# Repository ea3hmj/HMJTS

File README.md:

IMPORTANT, this repository is obsolete and has been replaced by the https://github.com/EA3HMJ-Tracking-Software-Suit

# EA3HMJ Antenna Tracking System

## Under construction
Please note that this is work-in-progress

## Description
This is an antenna tracking system that integrates dedicated hardware and software designed for amateur use in Earth–Moon–Earth communication (EME), radioastronomy, amateur Deep Sky Network (DSN) and other Space Communications applications where accurate and high precision tracking are required. 

Proper use of the system requires electronics knowledge and some software skills. Thus, it is only recommended to users with previous experience with antenna tracking systems.

The hardware components of this system are specifically selected to support the software applications that run on it. These components include a DishController unit -including a ESP32 microcontroller unit (MCU), DC motor driver board with high-performance and high-current driver devices, RS485 input/output devices and DC voltage step-up converter-, other peripherals like a variety of absolute digital encoders and inclinometers to sense the motion and position of the motorized slewing drive system and a remote-control unit.

In order to support single-turn and multiturn absolute encoders with parallel output interface there is also an optional Parallel to RS485 MODBUS converter board. Obviously, the latter is not needed if the sensors outputs are Modbus RS485 compliant.

The software components of this system are also specifically designed to work with the hardware components. This software includes the microcontroller and remote-control firmware, communications protocol, device drivers, and application software. 

The DishController MCU firmware controls and monitors the operation of the slewing drive motors, azimuth encoders, and elevation inclinometers.

The application software includes the DriverDish program, which is responsible for requesting data from the ephemeris server and communicating with the DishController unit, and a suite of server programs (JPLastroserver, Astroserver and Astronomyserver) that obtain the most accurate positioning data that is feasible and available from trustworthy sources. 

The integration of dedicated hardware and software in such a system provides several benefits. First, it improves system performance and reliability by allowing the DishController unit to directly access and control the specialized hardware components like the motor drivers and position sensors. This reduces overhead and improve response times. Second, it simplifies system design and development by providing a standardized set of hardware and software components that are optimized for narrow beamwidth antenna tracking. Third, in contrast to other antenna tracking system designs, the movement and position sensors are located at the last link of the movement chain to actively monitor the antenna's pointing direction. By doing so, the system is able to minimize the impact of mechanical tolerances and gear backslash.

The system is made up of three blocks that work together:
- Ephemeris servers ([Astroserver](https://github.com/ea3hmj/HMJTS/tree/main/ephemerides/astroserver), [JPLastroserver](https://github.com/ea3hmj/HMJTS/tree/main/ephemerides/JPLastroserver) and [Astronomyserver](https://github.com/ea3hmj/HMJTS/tree/main/ephemerides/astronmyserver))
- Control application in Windows OS ([DriverDish.App](https://github.com/ea3hmj/HMJTS/tree/main/DriverDish))
- Antenna Controller ([Controller Dish](https://github.com/ea3hmj/HMJTS/tree/main/controller%20dish/main%20board))

Utilities are also added:
- [AstroserverHelper.App](https://github.com/ea3hmj/HMJTS/tree/main/ephemerides/AstroserverHelper.App)
- Heatmap.App

## Disclaimer
This software -including the source and the whole package- and hardware are distributed "as is" without any representation or warranty of any kind, either express or implied. 

Please note that I am not able to provide support for this antenna tracking system. I designed and wrote it for myself and I am willing to share it here for those asking about my tracking system. I do not guarantee the accuracy or completeness of the information and materials distributed here. The software source has been tested on a real environment and scanned for viruses and has passed all tests.

I shall not be liable for any errors or omissions and shall not be responsible for any damages arising from the use of this antenna tracking system. I shall not be held responsible for any issues or problems that may arise from the use of it. 
By using any part of this antenna tracking system (software or hardware), you acknowledge and agree to the terms of this disclaimer.

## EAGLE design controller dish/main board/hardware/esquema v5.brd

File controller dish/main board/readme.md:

# CONTROLLER DISH
The controller allows to manage two motors with their corresponding position sensors.

## Documentation
For details, please read the document: [Dish Controller v4 ENG.pdf](docs/Dish%20Controller%20v4%20ENG.pdf)

## Disclaimer
This is a tracking systems designed for amateur use in Moonbounce, Radioastronomy and DSN. It requieres advanced skills of electronics and software, only recommended to users with previous experience with tracking systems.

Warning this software is distributed as is and I can not supply support. I write  it for myself and now I share it for other users that are asking about my tracking system.

This source and the whole package comes without warranty. It may or may not harm your computer or cell phone. Please use with care. Any damage cannot be related back to the author. The source has been tested on a real environment and scanned for viruses and has passed all tests.

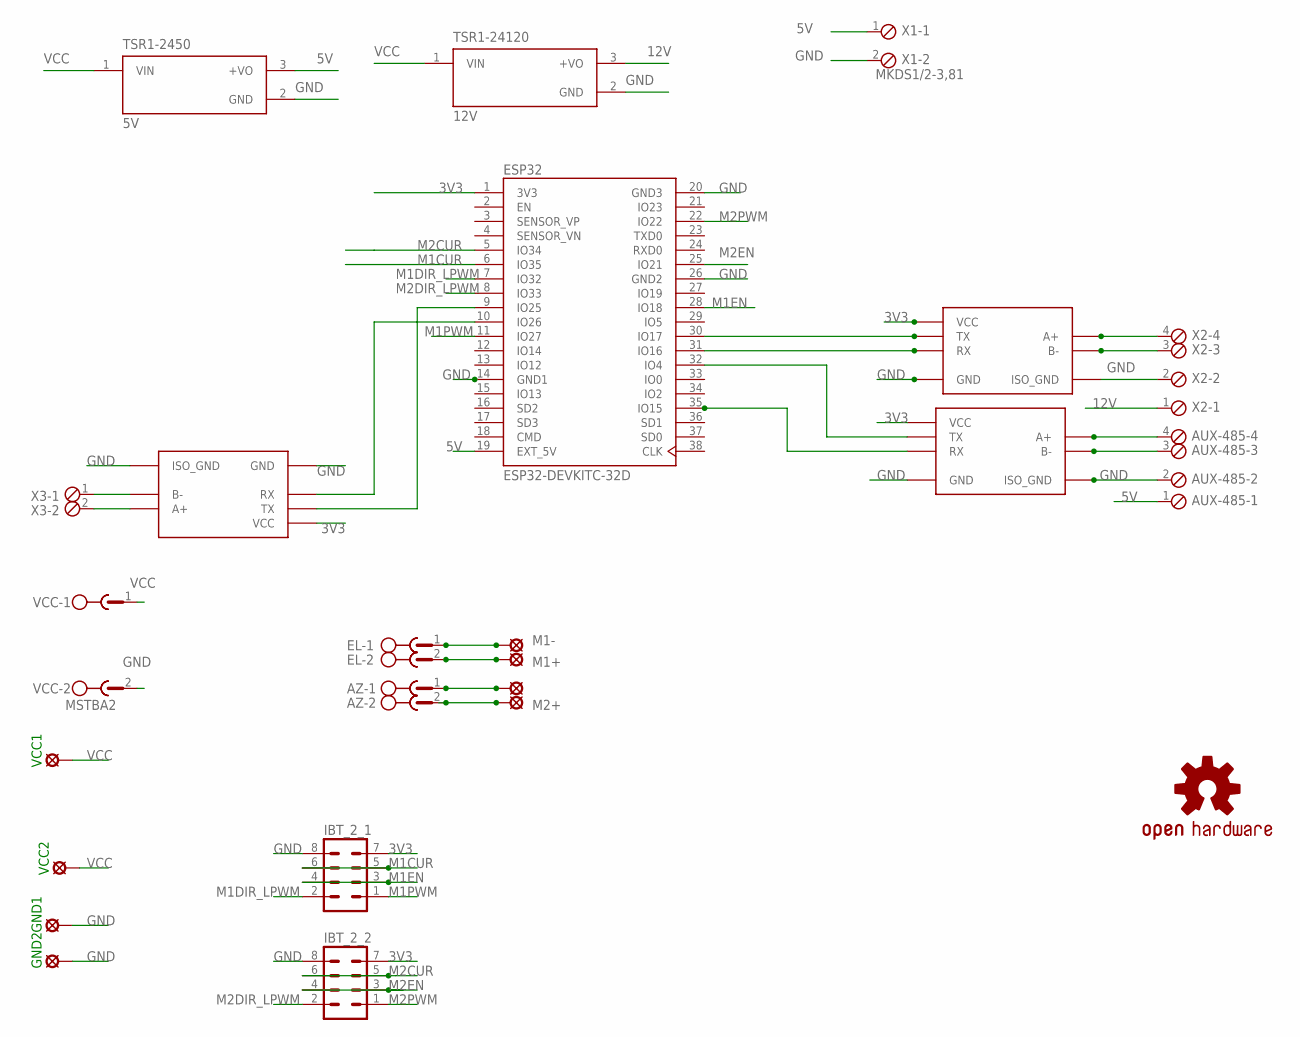
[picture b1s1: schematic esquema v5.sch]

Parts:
AUX-485: MKDS1/4-3,81; 4POL381
AZ: MSTBA2
EL: MSTBA2
ESP32: ESP32-DEVKITC-32D; MODULE_ESP32-DEVKITC-32D
GND1, GND2: LSP10
IBT_2_1: IBT_2_1; MA04-2
IBT_2_2: MA04-2
LOGO1: OSHW-LOGOMINI; OSHW-LOGO-MINI
M1+, M1-, M2+: LSP10
M2, M3, M4: LIMNOTECH_SMC_RS485
M2-: M2-; LSP10
TSR1-2450: 5V; CONV_K7803-500R3
TSR1-24120: 12V; CONV_K7803-500R3
VCC: MSTBA2
VCC1, VCC2: LSP10
X1, X3: MKDS1/2-3,81; 2POL381
X2: MKDS1/4-3,81; 4POL381

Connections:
3V3: ESP32.1 (3V3), IBT_2_1.7, IBT_2_2.7, M2.VCC, M3.VCC, M4.VCC
5V: AUX-485.1, ESP32.19 (EXT_5V), TSR1-2450.3 (+VO), X1.1
12V: TSR1-24120.3 (+VO), X2.1
GND: AUX-485.2, ESP32.14 (GND1), ESP32.20 (GND3), ESP32.26 (GND2), GND1.MP, GND2.MP, IBT_2_1.8, IBT_2_2.8, M2.GND, M2.GND_ISO (ISO_GND), M3.GND, M3.GND_ISO (ISO_GND), M4.GND, M4.GND_ISO (ISO_GND), TSR1-2450.2 (GND), TSR1-24120.2 (GND), VCC.2, X1.2, X2.2
M1+: EL.2, M1+.MP
M1-: EL.1, M1-.MP
M1CUR: ESP32.6 (IO35), IBT_2_1.5, IBT_2_1.6
M1DIR_LPWM: ESP32.7 (IO32), IBT_2_1.2
M1EN: ESP32.28 (IO18), IBT_2_1.3, IBT_2_1.4
M1PWM: ESP32.11 (IO27), IBT_2_1.1
M2+: AZ.2, M2+.MP
M2CUR: ESP32.5 (IO34), IBT_2_2.5, IBT_2_2.6
M2DIR_LPWM: ESP32.8 (IO33), IBT_2_2.2
M2EN: ESP32.25 (IO21), IBT_2_2.3, IBT_2_2.4
M2PWM: ESP32.22 (IO22), IBT_2_2.1
unnamed: M4.B-, X2.3
unnamed: AUX-485.4, M2.A+
unnamed: AZ.1, M2-.MP
unnamed: ESP32.32 (IO4), M2.TX
unnamed: ESP32.10 (IO26), M3.RX
unnamed: ESP32.9 (IO25), M3.TX
unnamed: ESP32.31 (IO16), M4.RX
unnamed: ESP32.30 (IO17), M4.TX
unnamed: M3.B-, X3.1
unnamed: M3.A+, X3.2
unnamed: ESP32.35 (IO15), M2.RX
unnamed: AUX-485.3, M2.B-
unnamed: M4.A+, X2.4
VCC: TSR1-2450.1 (VIN), TSR1-24120.1 (VIN), VCC.1, VCC1.MP, VCC2.MP

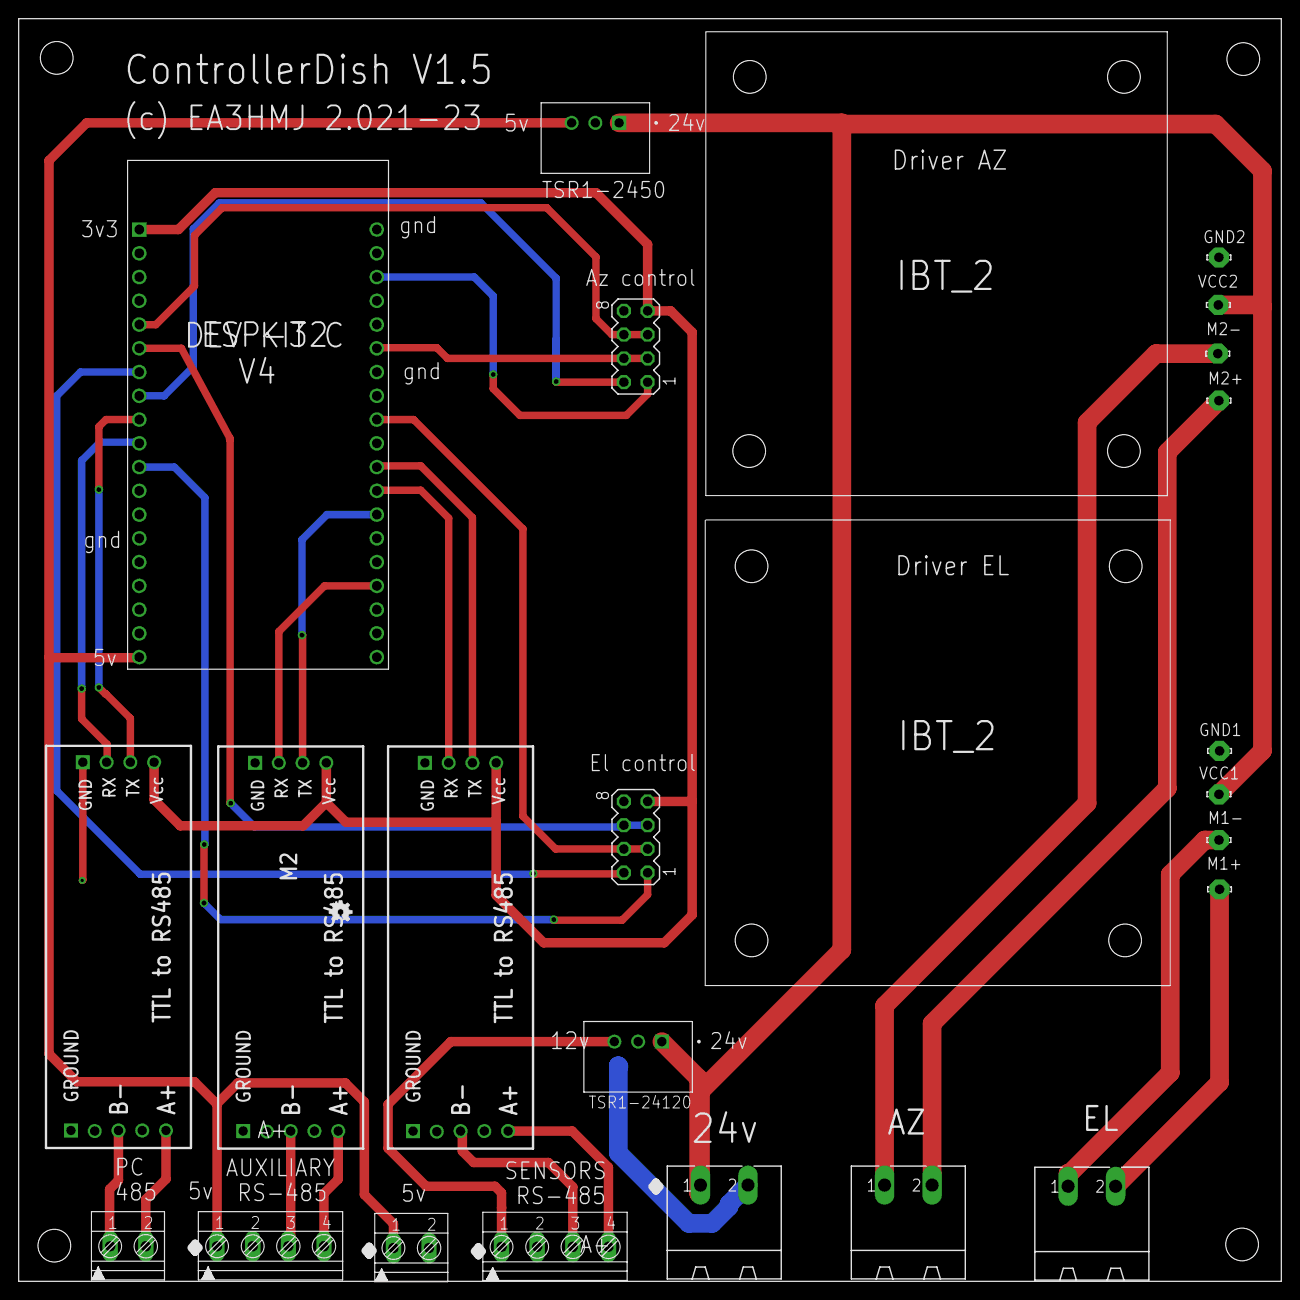
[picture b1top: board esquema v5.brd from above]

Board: 2 copper layers, 135.0 x 135.0 mm, 24 parts (0 on the bottom side), 29 nets.

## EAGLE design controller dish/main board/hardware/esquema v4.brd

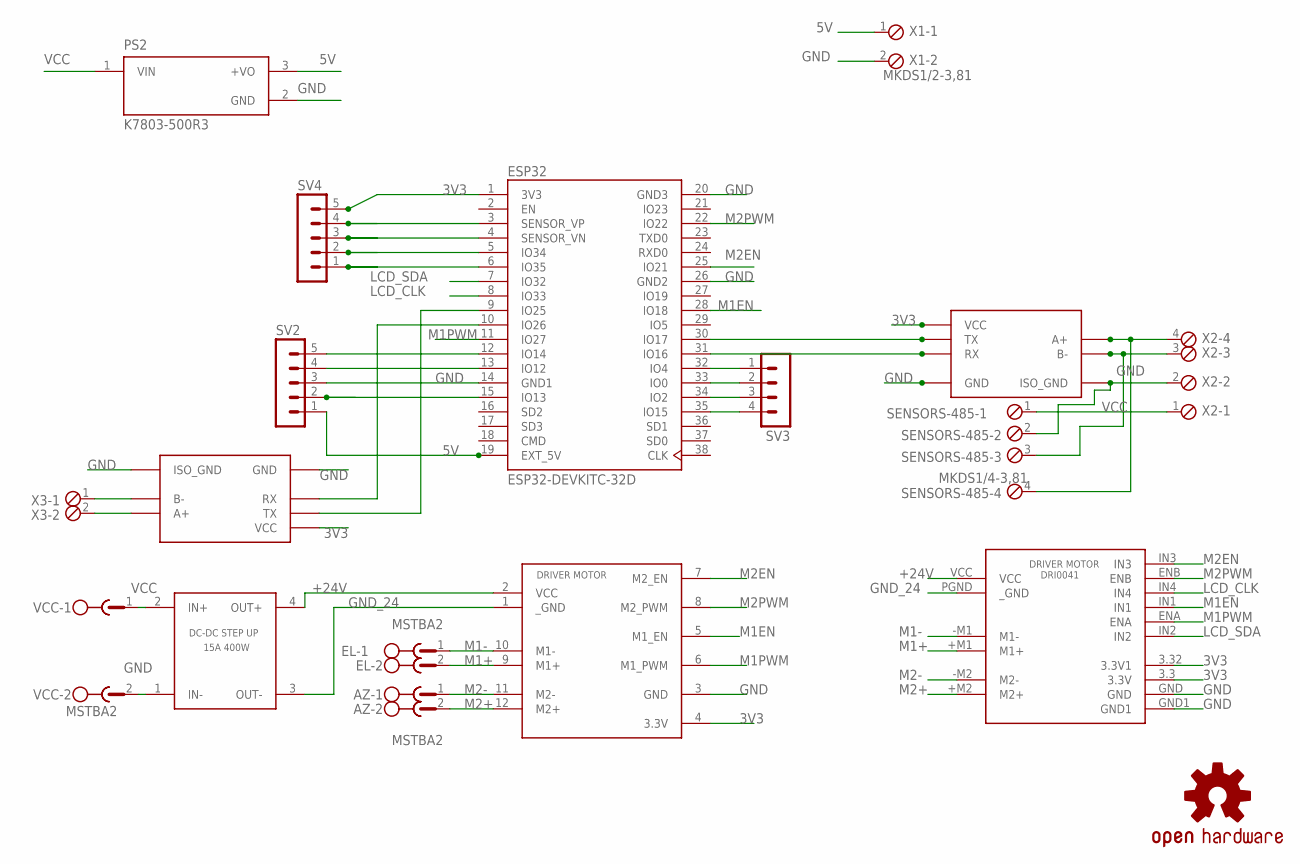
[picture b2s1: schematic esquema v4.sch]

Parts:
AZ: MSTBA2
EL: MSTBA2
ESP32: ESP32-DEVKITC-32D; MODULE_ESP32-DEVKITC-32D
LOGO1: OSHW-LOGOMINI; OSHW-LOGO-MINI
M1: DRIVER_MOTOR
M2: DC-DC_STRP_UP; DC-DC-SETP-UP
M3, M4: LIMNOTECH_SMC_RS485
PS2: K7803-500R3; CONV_K7803-500R3
SENSORS-485: MKDS1/4-3,81; 4POL381
SV2, SV4: MA05-1
SV3: MA04-1
U$2: DRIVER_DRI0041; DRI0041
VCC: MSTBA2
X1, X3: MKDS1/2-3,81; 2POL381
X2: MKDS1/4-3,81; 4POL381

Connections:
3V3: ESP32.1 (3V3), M1.4 (3.3V), M3.VCC, M4.VCC, SV4.5, U$2.3.3 (3.3V), U$2.3.32 (3.3V1)
5V: ESP32.19 (EXT_5V), PS2.3 (+VO), SV2.1, X1.1
+24V: M1.2 (VCC), M2.4 (OUT+), U$2.VCC
GND: ESP32.14 (GND1), ESP32.20 (GND3), ESP32.26 (GND2), M1.3 (GND), M2.1 (IN-), M3.GND, M3.GND_ISO (ISO_GND), M4.GND, M4.GND_ISO (ISO_GND), PS2.2 (GND), SENSORS-485.2, SV2.3, U$2.GND, U$2.GND1, VCC.2, X1.2, X2.2
GND_24: M1.1 (_GND), M2.3 (OUT-), U$2.PGND (_GND)
LCD_CLK: ESP32.8 (IO33), U$2.IN4
LCD_SDA: ESP32.7 (IO32), U$2.IN2
M1+: EL.2, M1.9 (M1+), U$2.+M1 (M1+)
M1-: EL.1, M1.10 (M1-), U$2.-M1 (M1-)
M1EN: ESP32.28 (IO18), M1.5 (M1_EN), U$2.IN1
M1PWM: ESP32.11 (IO27), M1.6 (M1_PWM), U$2.ENA
M2+: AZ.2, M1.12 (M2+), U$2.+M2 (M2+)
M2-: AZ.1, M1.11 (M2-), U$2.-M2 (M2-)
M2EN: ESP32.25 (IO21), M1.7 (M2_EN), U$2.IN3
M2PWM: ESP32.22 (IO22), M1.8 (M2_PWM), U$2.ENB
unnamed: M4.B-, SENSORS-485.3, X2.3
unnamed: M4.A+, SENSORS-485.4, X2.4
unnamed: ESP32.3 (SENSOR_VP), SV4.4
unnamed: ESP32.4 (SENSOR_VN), SV4.3
unnamed: ESP32.10 (IO26), M3.RX
unnamed: ESP32.9 (IO25), M3.TX
unnamed: ESP32.31 (IO16), M4.RX
unnamed: ESP32.30 (IO17), M4.TX
unnamed: M3.B-, X3.1
unnamed: M3.A+, X3.2
unnamed: ESP32.5 (IO34), SV4.2
unnamed: ESP32.6 (IO35), SV4.1
unnamed: ESP32.15 (IO13), SV2.2
unnamed: ESP32.13 (IO12), SV2.4
unnamed: ESP32.12 (IO14), SV2.5
unnamed: ESP32.32 (IO4), SV3.1
unnamed: ESP32.33 (IO0), SV3.2
unnamed: ESP32.34 (IO2), SV3.3
unnamed: ESP32.35 (IO15), SV3.4
VCC: M2.2 (IN+), PS2.1 (VIN), SENSORS-485.1, VCC.1, X2.1

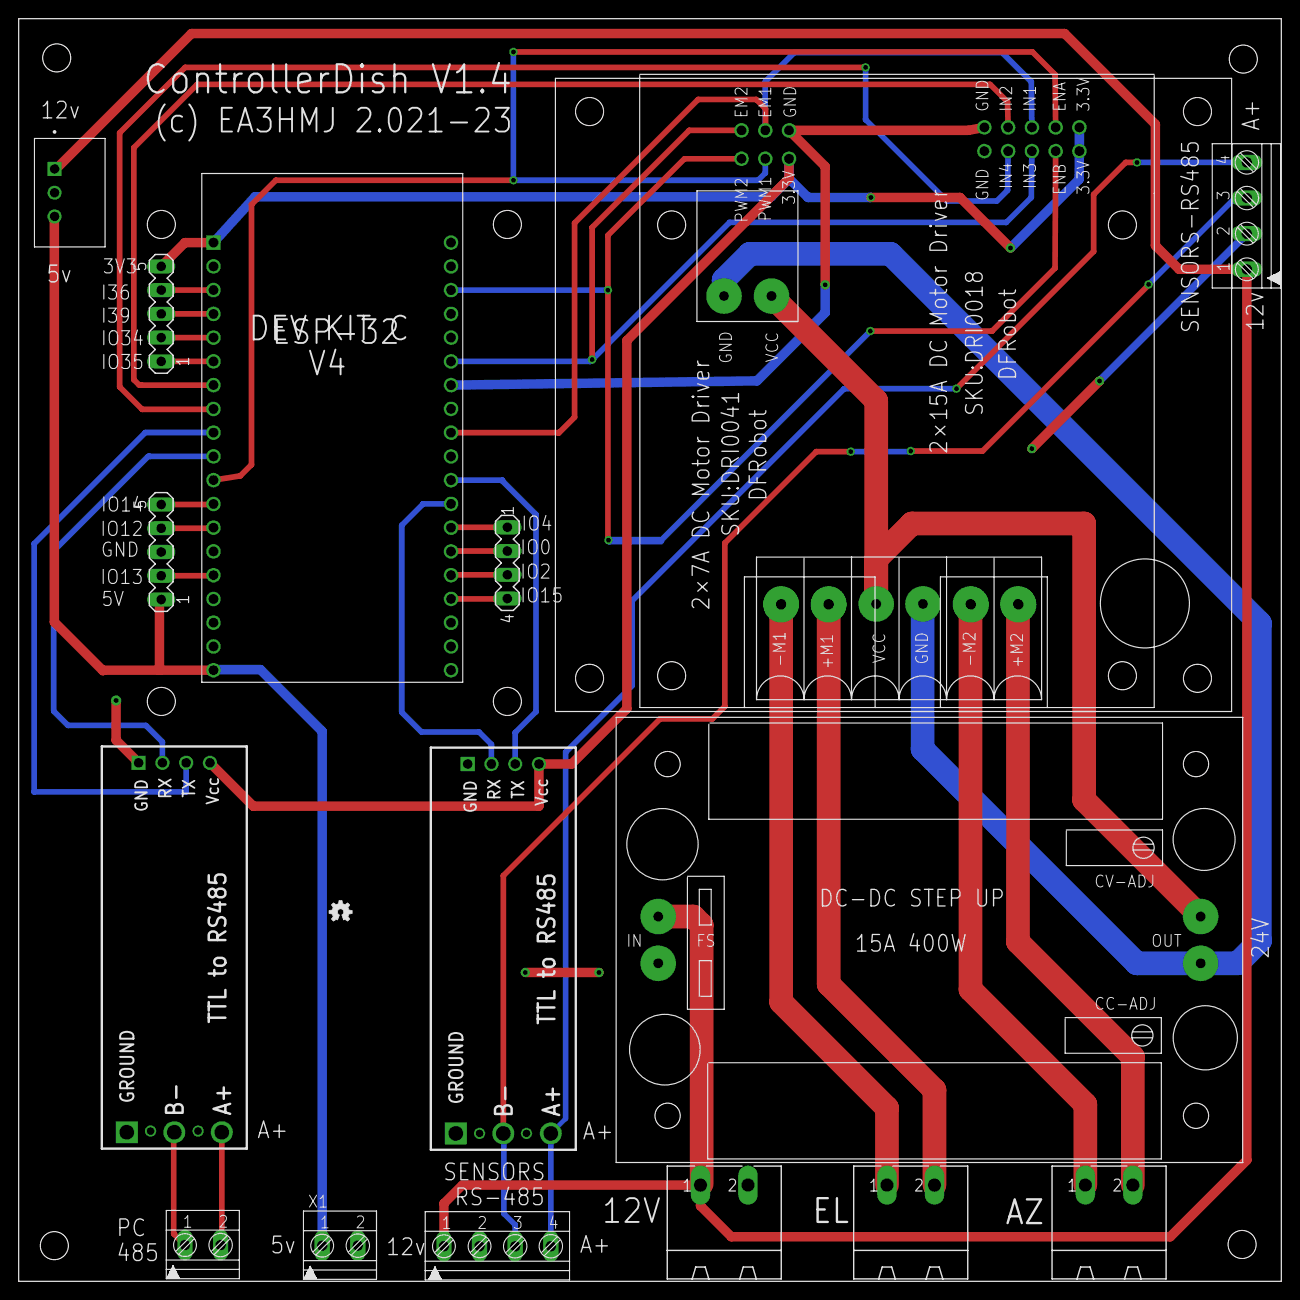
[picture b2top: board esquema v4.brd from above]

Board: 2 copper layers, 135.0 x 135.0 mm, 18 parts (0 on the bottom side), 35 nets.

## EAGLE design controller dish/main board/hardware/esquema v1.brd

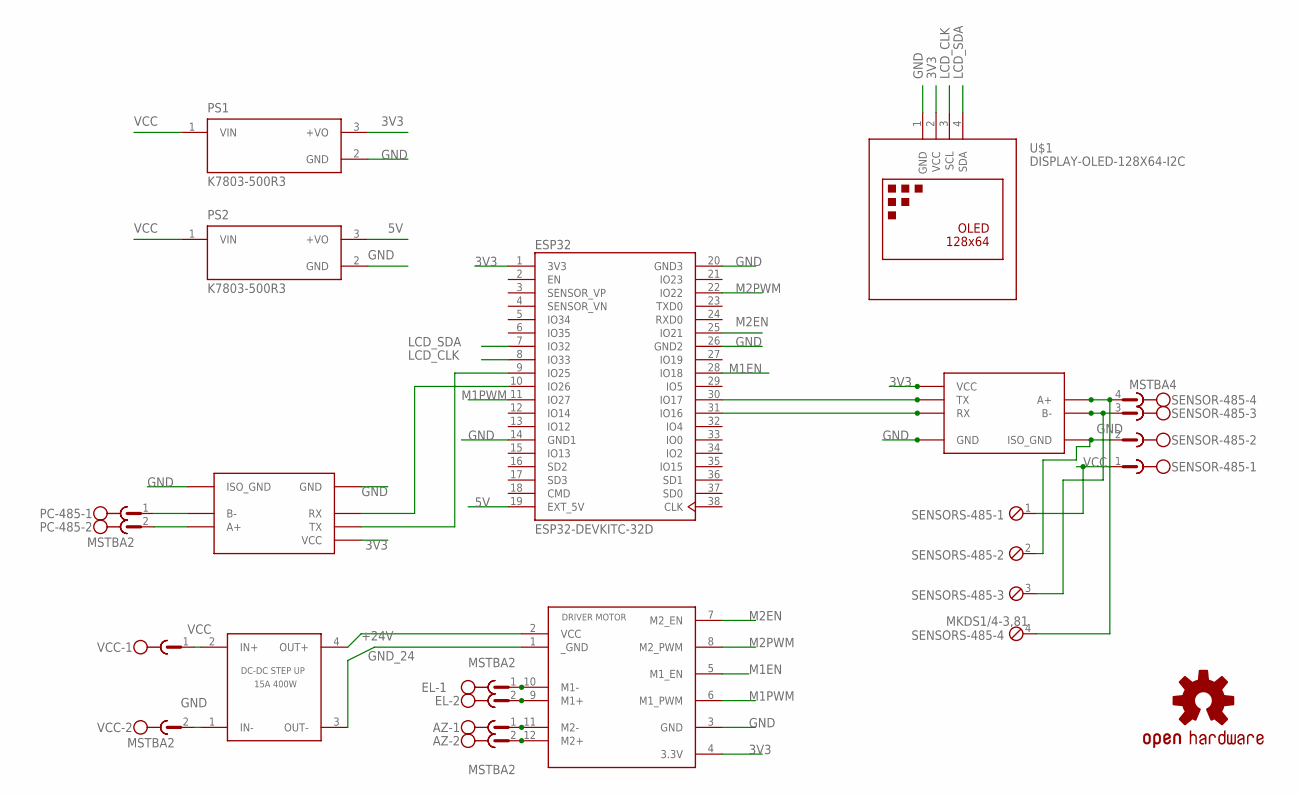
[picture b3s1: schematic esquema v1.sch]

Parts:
AZ: MSTBA2
EL: MSTBA2
ESP32: ESP32-DEVKITC-32D; MODULE_ESP32-DEVKITC-32D
LOGO1: OSHW-LOGOMINI; OSHW-LOGO-MINI
M1: DRIVER_MOTOR
M2: DC-DC_STRP_UP; DC-DC-SETP-UP
M3, M4: LIMNOTECH_SMC_RS485
PC-485: MSTBA2
PS1, PS2: K7803-500R3; CONV_K7803-500R3
SENSOR-485: MSTBA4
SENSORS-485: MKDS1/4-3,81; 4POL381
U$1: DISPLAY-OLED-128X64-I2C
VCC: MSTBA2

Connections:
3V3: ESP32.1 (3V3), M1.4 (3.3V), M3.VCC, M4.VCC, PS1.3 (+VO), U$1.2 (VCC)
5V: ESP32.19 (EXT_5V), PS2.3 (+VO)
+24V: M1.2 (VCC), M2.4 (OUT+)
GND: ESP32.14 (GND1), ESP32.20 (GND3), ESP32.26 (GND2), M1.3 (GND), M2.1 (IN-), M3.GND, M3.GND_ISO (ISO_GND), M4.GND, M4.GND_ISO (ISO_GND), PS1.2 (GND), PS2.2 (GND), SENSOR-485.2, SENSORS-485.2, U$1.1 (GND), VCC.2
GND_24: M1.1 (_GND), M2.3 (OUT-)
LCD_CLK: ESP32.8 (IO33), U$1.3 (SCL)
LCD_SDA: ESP32.7 (IO32), U$1.4 (SDA)
M1EN: ESP32.28 (IO18), M1.5 (M1_EN)
M1PWM: ESP32.11 (IO27), M1.6 (M1_PWM)
M2EN: ESP32.25 (IO21), M1.7 (M2_EN)
M2PWM: ESP32.22 (IO22), M1.8 (M2_PWM)
unnamed: M4.B-, SENSOR-485.3, SENSORS-485.3
unnamed: M4.A+, SENSOR-485.4, SENSORS-485.4
unnamed: EL.2, M1.9 (M1+)
unnamed: AZ.2, M1.12 (M2+)
unnamed: ESP32.10 (IO26), M3.RX
unnamed: ESP32.9 (IO25), M3.TX
unnamed: ESP32.31 (IO16), M4.RX
unnamed: ESP32.30 (IO17), M4.TX
unnamed: M3.B-, PC-485.1
unnamed: M3.A+, PC-485.2
unnamed: AZ.1, M1.11 (M2-)
unnamed: EL.1, M1.10 (M1-)
VCC: M2.2 (IN+), PS1.1 (VIN), PS2.1 (VIN), SENSOR-485.1, SENSORS-485.1, VCC.1

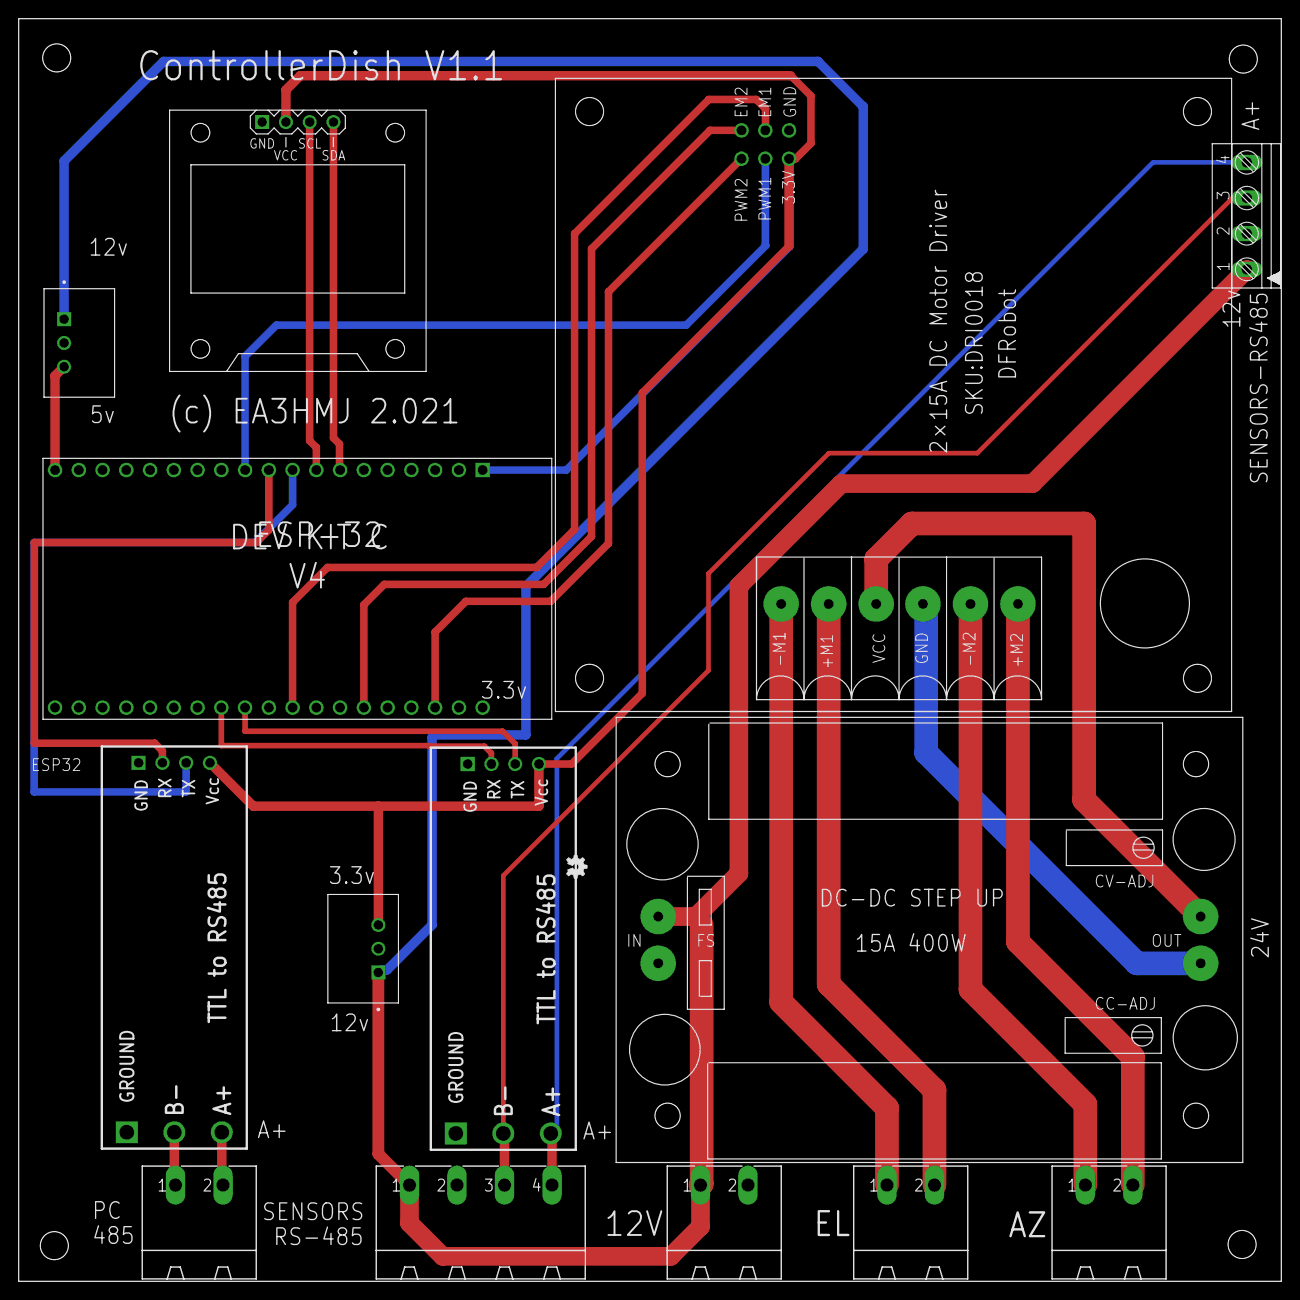
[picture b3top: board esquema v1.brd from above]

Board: 2 copper layers, 135.0 x 135.0 mm, 15 parts (0 on the bottom side), 24 nets.

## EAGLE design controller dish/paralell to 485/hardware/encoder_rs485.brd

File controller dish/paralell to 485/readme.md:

# CONVERTER PARALEL TO MODBUS-RTU RS-485
Interface for reading a 13-bit parallel encoder and converting it to RS-485 MOD-BU protocol.

## Documentation
For details, please read the document: [Encoder optico v2 ENG.pdf](docs/Encoder%20optico%20v2%20ENG.pdf)

## External library 
[ModbusSlave](https://github.com/yaacov/ArduinoModbusSlave)

## Updates

Download the firmware in [latest release page](https://github.com/ea3hmj/HMJTS/blob/main/controller%20dish/paralell%20to%20485/software/interface%20485.rar)

Use ST-LINK2 to program the board.

[Drivers for ST-LINK2 windows available here](https://github.com/ea3hmj/HMJTS/blob/main/controller%20dish/paralell%20to%20485/software/ST-LINK_USB_V2_1_Driver.rar)

## Disclaimer
This is an antenna tracking system (software and hardware) designed for amateur use in Earth–Moon–Earth communication (EME), radioastronomy, amateur Deep Sky Network (DSN) and other Space Communication applications where accurate and high precision tracking are required. 
Proper use of the system requires electronics knowledge and some software skills. Thus, it is only recommended to users with previous experience with antenna tracking systems.

This software -including the source and the whole package- and hardware are distributed "as is" without any representation or warranty of any kind, either express or implied. 

Please note that I am not able to provide support for this antenna tracking system. I designed and wrote it for myself and I am willing to share it here for those asking about my tracking system. I do not guarantee the accuracy or completeness of the information and materials distributed here. The software source has been tested on a real environment and scanned for viruses and has passed all tests.

I shall not be liable for any errors or omissions and shall not be responsible for any damages arising from the use of this antenna tracking system. I shall not be held responsible for any issues or problems that may arise from the use of it. 
By using any part of this antenna tracking system (software or hardware), you acknowledge and agree to the terms of this disclaimer.

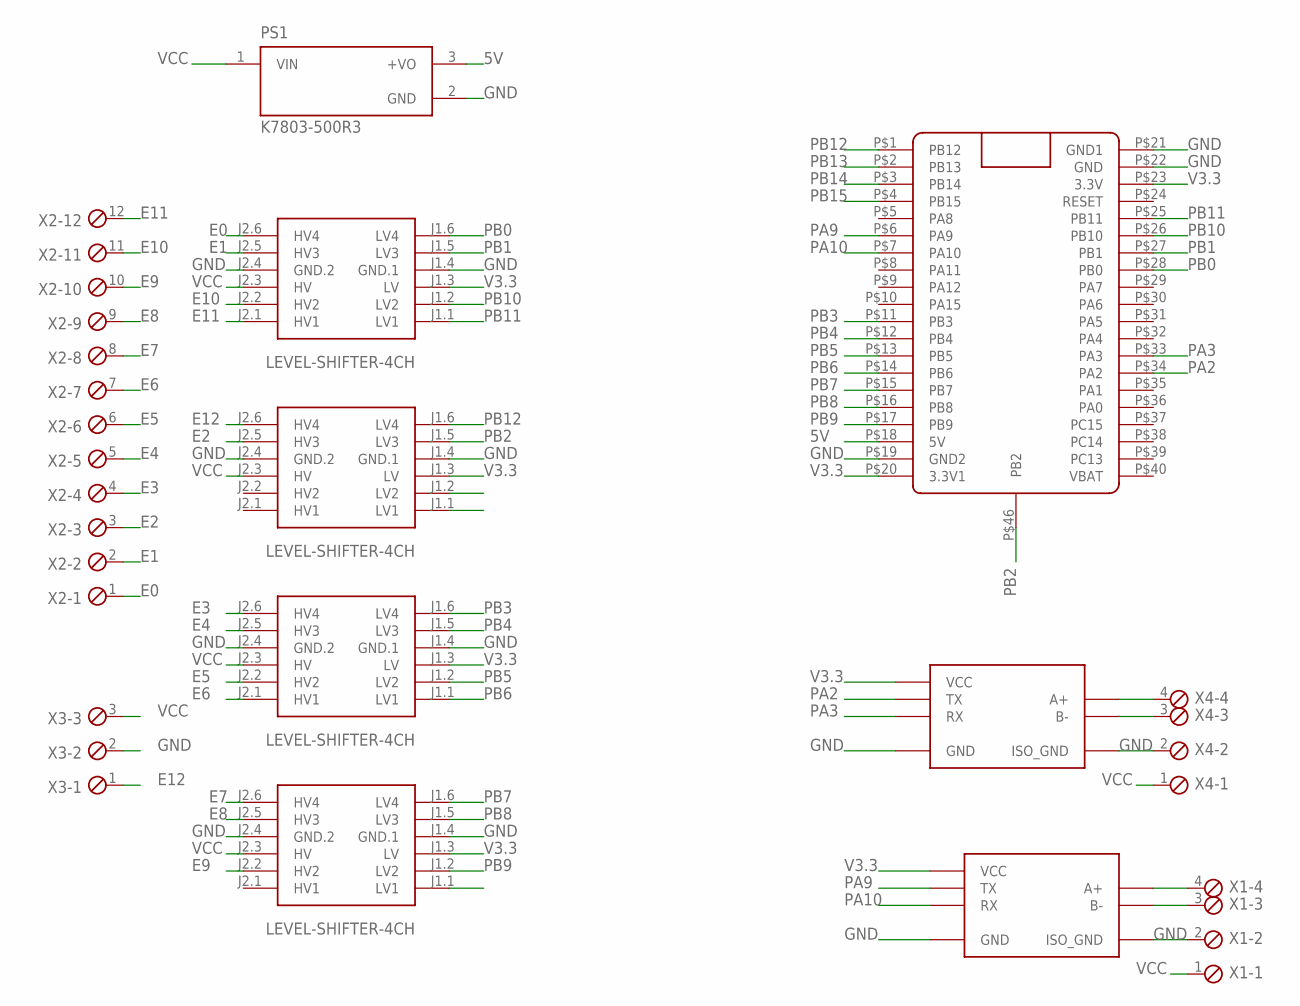
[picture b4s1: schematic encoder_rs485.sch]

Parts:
PS1: K7803-500R3; CONV_K7803-500R3
U$1, U$7: LIMNOTECH_SMC_RS485
U$2, U$3, U$4, U$5: LEVEL-SHIFTER-4CH
U$6: BLUE_PILLADVANCED; BLUE_PILL_ADV
X1, X4: MKDS1/4-3,81; 4POL381
X2: MKDS1/12-3,81; 12POL381
X3: MKDS1/3-3,81; 3POL381

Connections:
5V: PS1.3 (+VO), U$6.P$18 (5V)
E0: U$2.J2.6 (HV4), X2.1
E1: U$2.J2.5 (HV3), X2.2
E2: U$3.J2.5 (HV3), X2.3
E3: U$4.J2.6 (HV4), X2.4
E4: U$4.J2.5 (HV3), X2.5
E5: U$4.J2.2 (HV2), X2.6
E6: U$4.J2.1 (HV1), X2.7
E7: U$5.J2.6 (HV4), X2.8
E8: U$5.J2.5 (HV3), X2.9
E9: U$5.J2.2 (HV2), X2.10
E10: U$2.J2.2 (HV2), X2.11
E11: U$2.J2.1 (HV1), X2.12
E12: U$3.J2.6 (HV4), X3.1
GND: PS1.2 (GND), U$1.GND, U$1.GND_ISO (ISO_GND), U$2.J1.4 (GND.1), U$2.J2.4 (GND.2), U$3.J1.4 (GND.1), U$3.J2.4 (GND.2), U$4.J1.4 (GND.1), U$4.J2.4 (GND.2), U$5.J1.4 (GND.1), U$5.J2.4 (GND.2), U$6.P$19 (GND2), U$6.P$21 (GND1), U$6.P$22 (GND), U$7.GND, U$7.GND_ISO (ISO_GND), X1.2, X3.2, X4.2
unnamed: U$1.B-, X1.3
unnamed: U$1.A+, X1.4
unnamed: U$7.B-, X4.3
unnamed: U$7.A+, X4.4
PA2: U$6.P$34 (PA2), U$7.TX
PA3: U$6.P$33 (PA3), U$7.RX
PA9: U$1.TX, U$6.P$6 (PA9)
PA10: U$1.RX, U$6.P$7 (PA10)
PB0: U$2.J1.6 (LV4), U$6.P$28 (PB0)
PB1: U$2.J1.5 (LV3), U$6.P$27 (PB1)
PB2: U$3.J1.5 (LV3), U$6.P$46 (PB2)
PB3: U$4.J1.6 (LV4), U$6.P$11 (PB3)
PB4: U$4.J1.5 (LV3), U$6.P$12 (PB4)
PB5: U$4.J1.2 (LV2), U$6.P$13 (PB5)
PB6: U$4.J1.1 (LV1), U$6.P$14 (PB6)
PB7: U$5.J1.6 (LV4), U$6.P$15 (PB7)
PB8: U$5.J1.5 (LV3), U$6.P$16 (PB8)
PB9: U$5.J1.2 (LV2), U$6.P$17 (PB9)
PB10: U$2.J1.2 (LV2), U$6.P$26 (PB10)
PB11: U$2.J1.1 (LV1), U$6.P$25 (PB11)
PB12: U$3.J1.6 (LV4), U$6.P$1 (PB12)
PB13: U$6.P$2 (PB13)
PB14: U$6.P$3 (PB14)
PB15: U$6.P$4 (PB15)
V3.3: U$1.VCC, U$2.J1.3 (LV), U$3.J1.3 (LV), U$4.J1.3 (LV), U$5.J1.3 (LV), U$6.P$20 (3.3V1), U$6.P$23 (3.3V), U$7.VCC
VCC: PS1.1 (VIN), U$2.J2.3 (HV), U$3.J2.3 (HV), U$4.J2.3 (HV), U$5.J2.3 (HV), X1.1, X3.3, X4.1

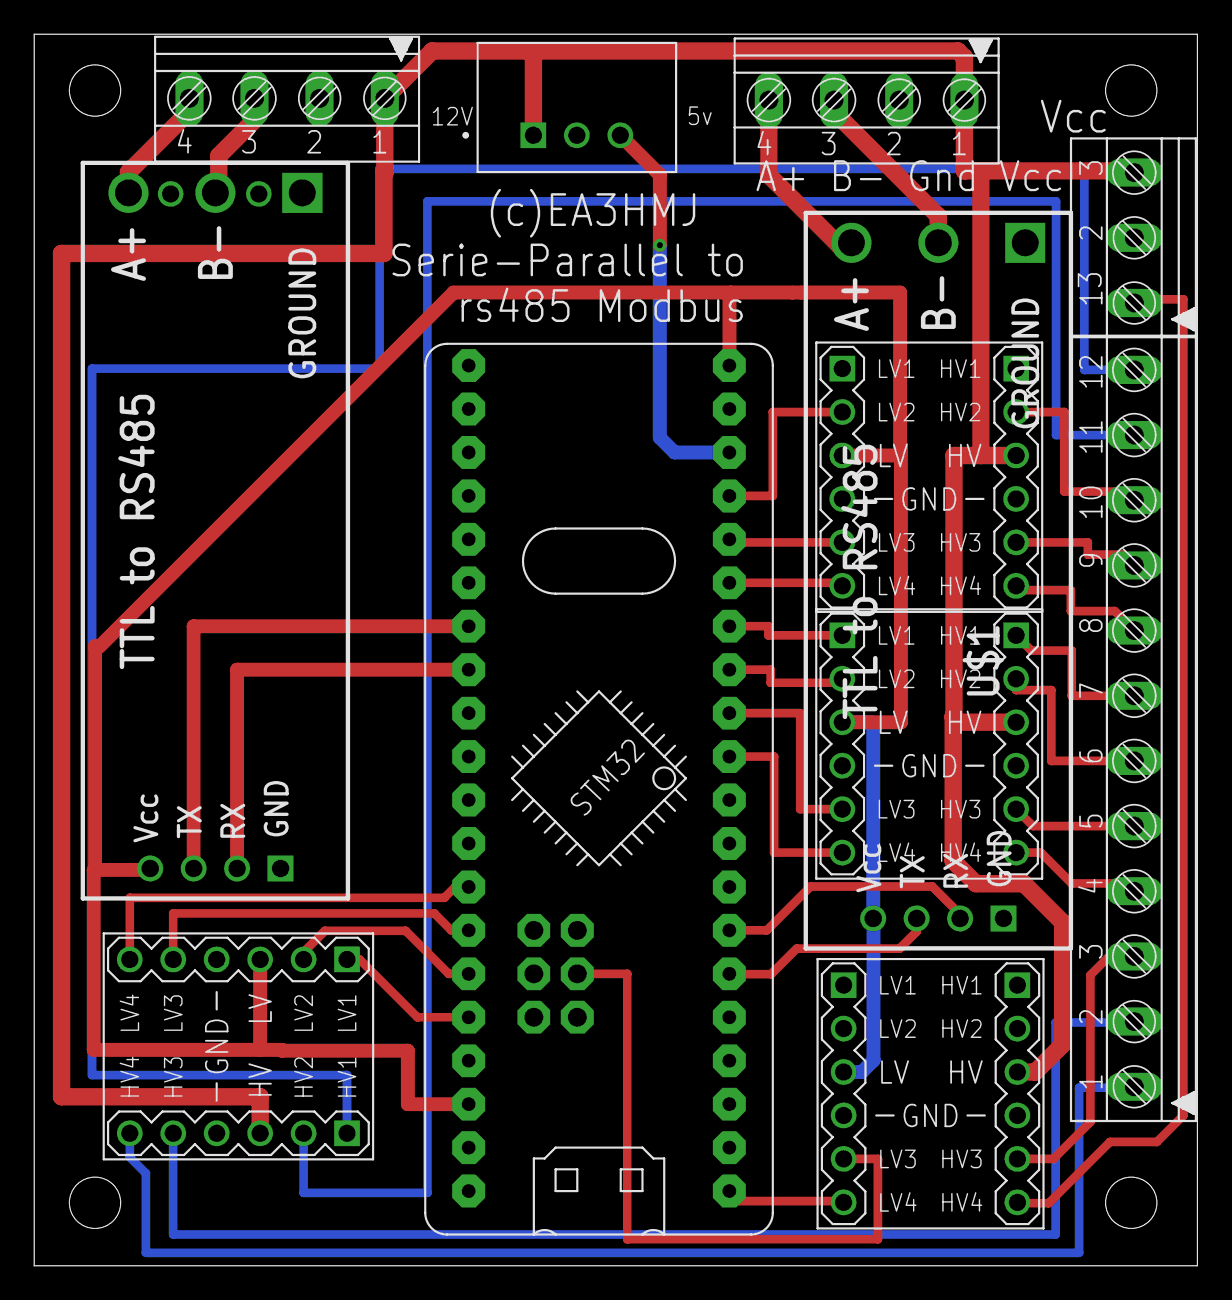
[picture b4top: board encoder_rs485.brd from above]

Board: 2 copper layers, 68.0 x 72.0 mm, 12 parts (0 on the bottom side), 38 nets.

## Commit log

2022-09-20 Create \img
2022-09-20 Create nill
2022-09-26 Add files via upload
    Initial commit
2023-02-04 new relase
2023-02-09 Bug PB2 solved, need change 10K R4 for 0R
2023-02-11 new release
2023-02-11 new version 2.1.143
2023-02-11 update 11/02/2023
2023-02-11 release 11/02/2023
2023-02-14 relase 14/02/23
2023-02-19 release 1.0.827
2023-04-23 new version
2023-04-23 suport command <body>?D
2023-04-26 new project
2023-04-26 new release, minor bugs
2023-05-07 Suport hardware 1.5
2023-05-07 minor update
2023-05-08 New hardware version
2023-05-08 new file
2023-05-08 SigDigger doppler tool support
2023-05-15 Drift bug
2023-05-20 new release 1.0.263
2023-05-21 New version 1.0.273
2023-05-21 new doc
2023-06-11 Version 1.0287
    Bug when no data
2023-07-19 New release multi server
2023-07-24 Body server update
2023-08-01 Auto position
    Auto position as a function of SN received
2023-08-05 Update setup program
2023-08-05 Update setup
2023-08-25 Add snensor azimuth 16 bits
2023-08-25 Add search in spacecraft-satellite form
2023-09-24 mew doc

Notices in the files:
parts and their libraries:
SparkFun-Aesthetics: Licensing: Creative Commons ShareAlike 4.0 International - https://creativecommons.org/licenses/by-sa/4.0
diy-modules: Released under the Creative Commons Attribution 4.0 International License: http://creativecommons.org/licenses/by/4.0
